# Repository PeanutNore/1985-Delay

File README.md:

# 1985-Delay
A Digital Delay pedal for guitar built around the AVR128DA28 MCU
    
This program is distributed in the hope that it will be useful,
but WITHOUT ANY WARRANTY; without even the implied warranty of
MERCHANTABILITY or FITNESS FOR A PARTICULAR PURPOSE.

 * Copyright 2025 Samuel Brown. All Rights Reservered.
 * 
 * Licensed under Creative Commons CC-BY-NC-SA 4.0
 * https://creativecommons.org/licenses/by-nc-sa/4.0/
 * 
 * You are free to share and adapt this software for non-
 * commercial purposes provided that you give appropriate 
 * credit and attribution, and distribute your contributions 
 * under the same CC-BY-NC-SA license.
 * 
 * For commercial licensing contact sam.brown.rit08@gmail.com

The maximum delay time available depends on the sample rate used and the bit depth of delay samples.
Main branch (1985_Delay) provides 1.4 seconds of delay at 10kHz and 8 bits and is tested and working with minor issues.
Highres branch (1985_Delay_Highres) provides 700ms of delay at 10kHz and 12 bits and is untested.

Adjust the sample rate as desired to balance available delay time and audio quality.

To use this software you will need:
* Arduino IDE version 1.8.19 or greater
* DxCore library for AVR128DA28 support (https://github.com/SpenceKonde/DxCore)
* Any USB to UPDI programmer. I recommend the Adafruit UPDI Friend because it is easy to use and under $20
* An AVR128DA28 MCU and appropriate supporting circuitry. Refer to the KiCad schematic and board files included in this repository.

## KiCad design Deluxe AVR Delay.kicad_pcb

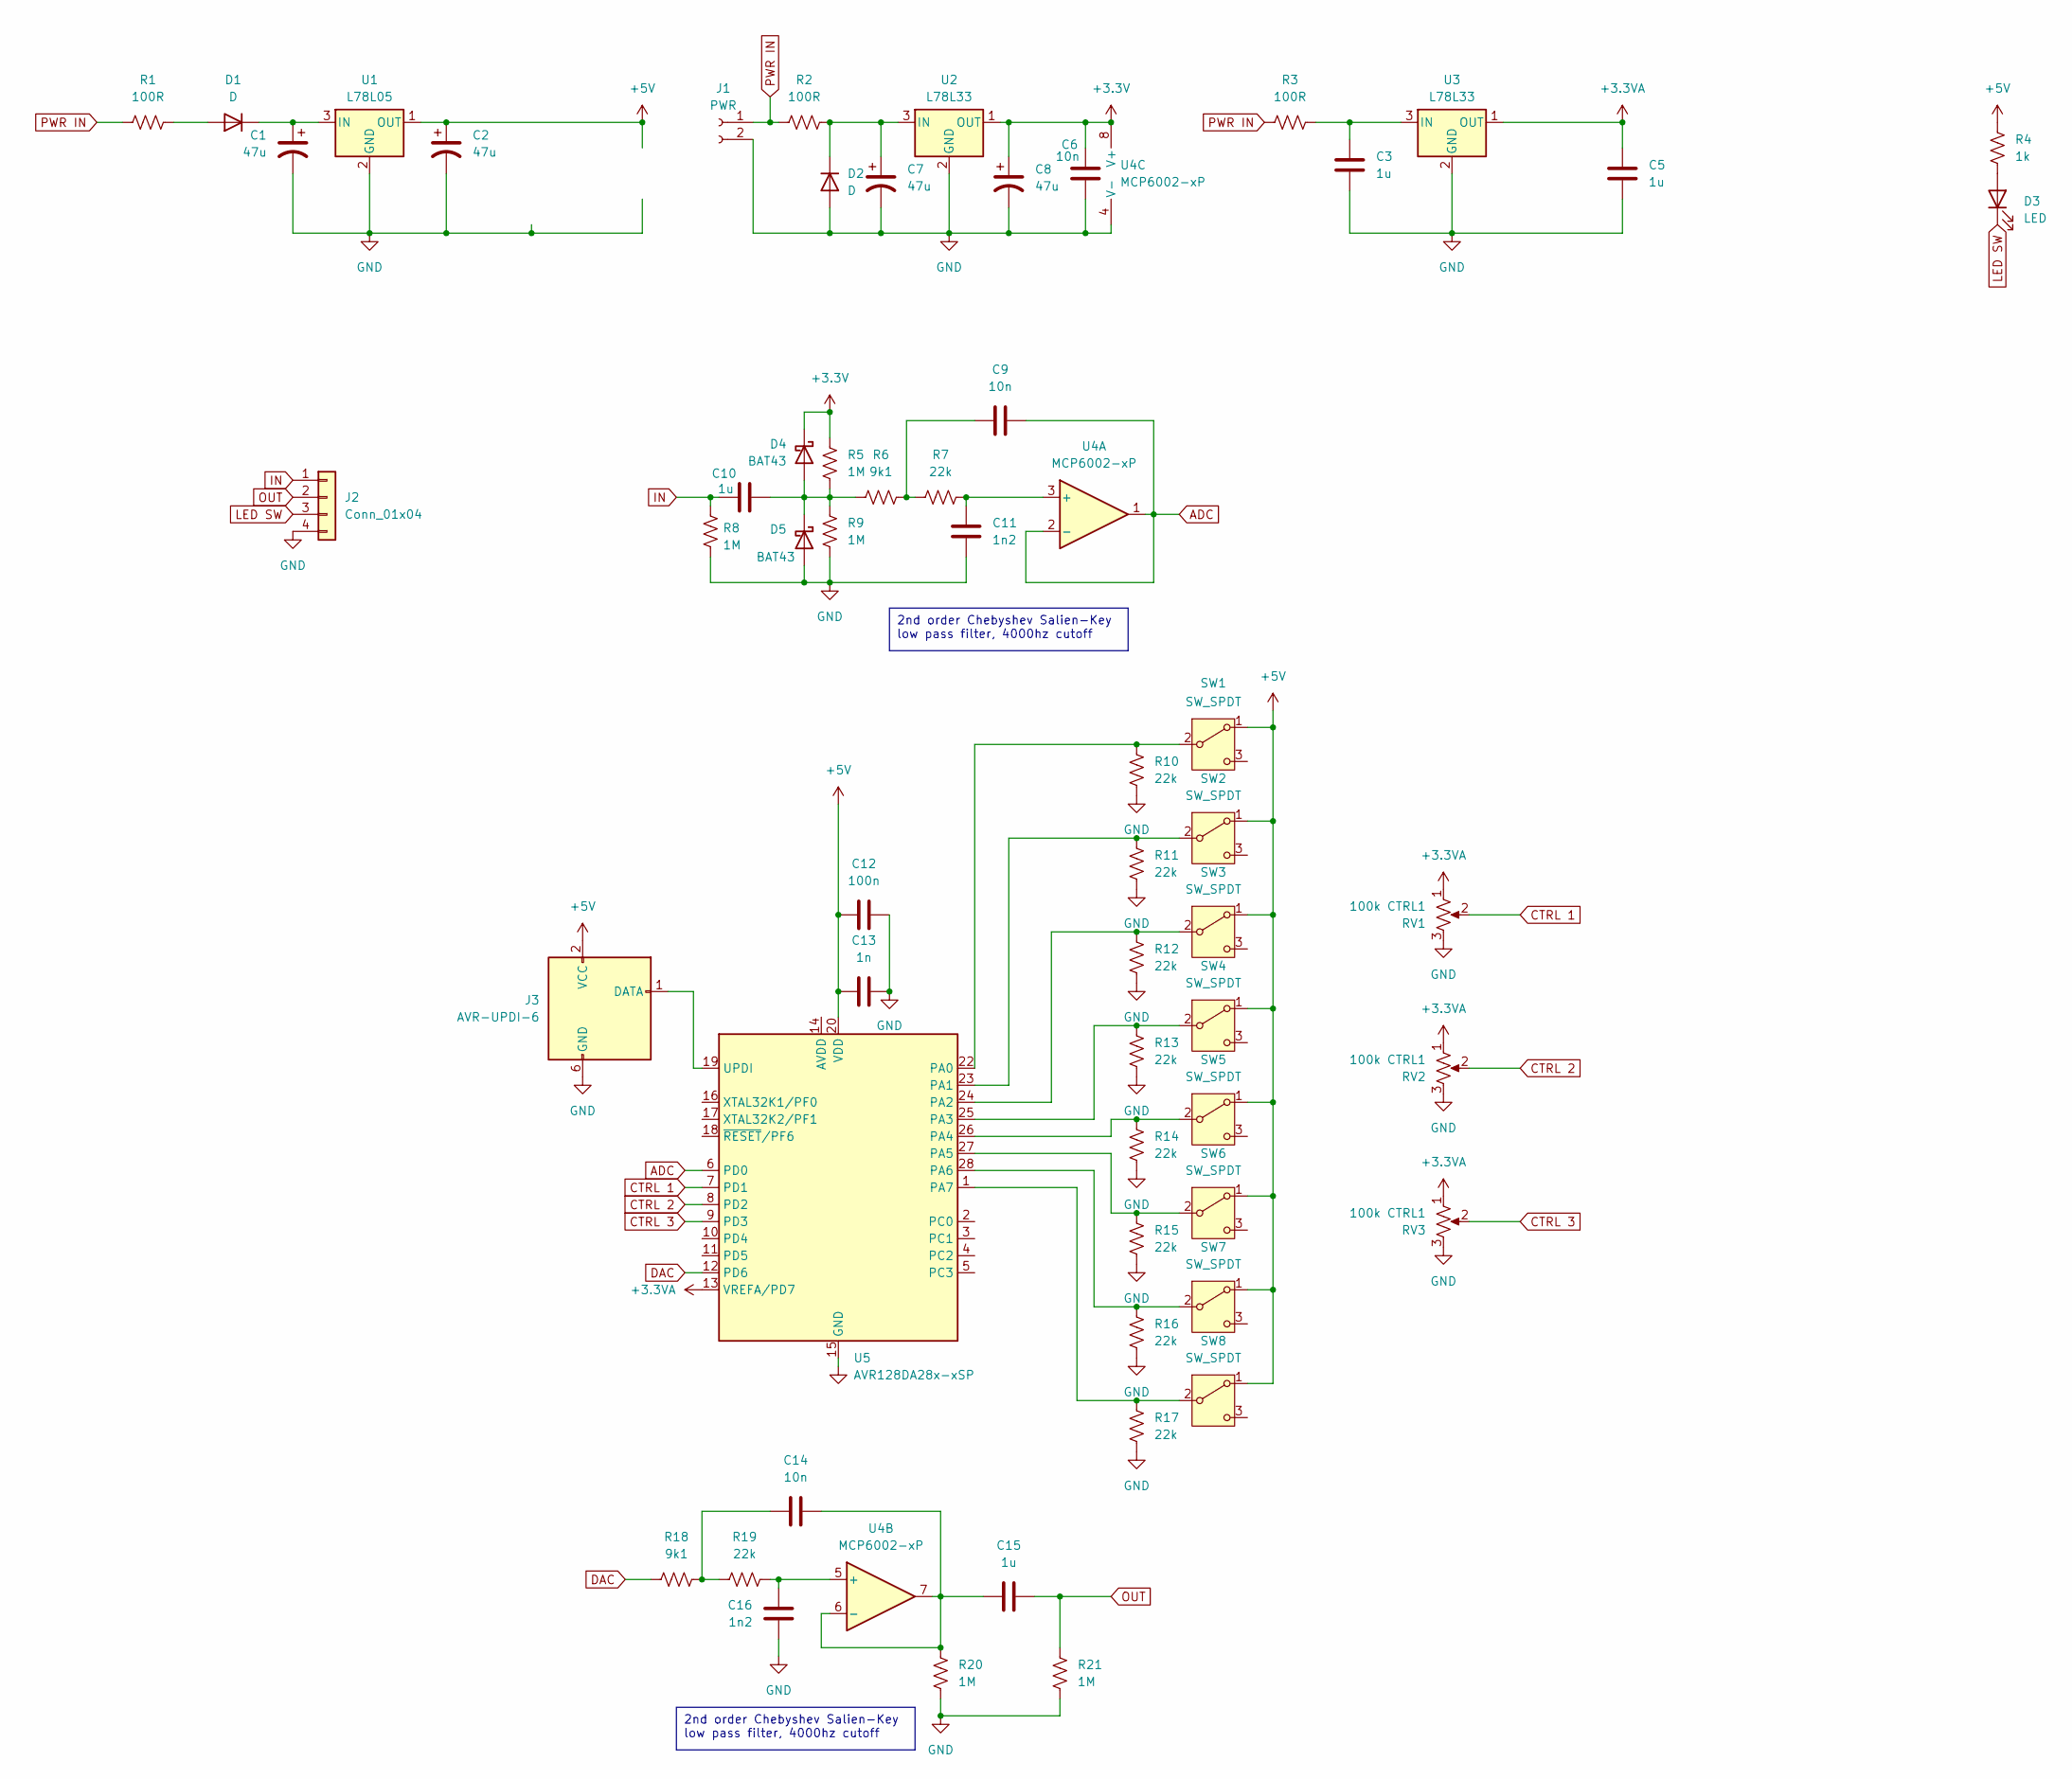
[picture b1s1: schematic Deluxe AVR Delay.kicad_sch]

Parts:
C1, C2, C7, C8: 47u; CP_Radial_D5.0mm_P2.50mm
C3, C5: 1u; C_1210_3225Metric
C6, C9, C14: 10n; C_0603_1608Metric
C10, C15: 1u; C_Rect_L7.0mm_W6.5mm_P5.00mm
C11, C16: 1n2; C_0603_1608Metric
C12: 100n; C_0603_1608Metric
C13: 1n; C_0603_1608Metric
D1, D2: D; D_DO-35_SOD27_P7.62mm_Horizontal
D3: LED; LED_D3.0mm
D4, D5: BAT43; D_DO-35_SOD27_P7.62mm_Horizontal
J1: PWR; PinHeader_1x02_P2.54mm_Vertical
J2: Conn_01x04; PinHeader_1x04_P2.54mm_Vertical
J3: AVR-UPDI-6; PinHeader_2x03_P2.54mm_Vertical
R1, R2, R3: 100R; R_Axial_DIN0207_L6.3mm_D2.5mm_P7.62mm_Horizontal
R4: 1k; R_0805_2012Metric
R5, R8, R9, R20, R21: 1M; R_0805_2012Metric
R6, R18: 9k1; R_0805_2012Metric
R7, R10, R11, R12, R13, R14, R15, R16, R17, R19: 22k; R_0805_2012Metric
RV1, RV2, RV3: 100k CTRL1; RV16AF-41
SW1, SW2, SW3, SW4, SW5, SW6, SW7, SW8: SW_SPDT; 2MS1T1B3M2QES
U1: L78L05; SOT-89-3
U2, U3: L78L33; SOT-89-3
U4: MCP6002-xP; DIP-8_W7.62mm_Socket
U5: AVR128DA28x-xSP; DIP-28_W7.62mm

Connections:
+3.3V: C6.1, C8.1, D4.1 (K), R5.1, U2.1 (OUT), U4.8 (V+)
+3.3VA: C5.2, RV1.1, RV2.1, RV3.1, U3.1 (OUT), U5.13 (VREFA/PD7)
+5V: C2.1, C12.1, C13.1, J3.2 (VCC), R4.1, SW1.1 (A), SW2.1 (A), SW3.1 (A), SW4.1 (A), SW5.1 (A), SW6.1 (A), SW7.1 (A), SW8.1 (A), U1.1 (OUT), U5.20 (VDD)
ADC: C9.2, U4.1, U4.2 (-), U5.6 (PD0)
CTRL 1: RV1.2, U5.7 (PD1)
CTRL 2: RV2.2, U5.8 (PD2)
CTRL 3: RV3.2, U5.9 (PD3)
DAC: R18.1, U5.12 (PD6)
GND: C1.2, C2.2, C3.1, C5.1, C6.2, C7.2, C8.2, C11.2, C12.2, C13.2, C16.2, D2.2 (A), D5.2 (A), J1.2, J2.4, J3.6 (GND), R8.2, R9.2, R10.1, R11.1, R12.1, R13.1, R14.1, R15.1, R16.1, R17.1, R20.2, R21.2, RV1.3, RV2.3, RV3.3, U1.2 (GND), U2.2 (GND), U3.2 (GND), U4.4 (V-), U5.15 (GND), U5.21 (GND)
IN: C10.1, J2.1, R8.1
LED SW: D3.1 (K), J2.3
unnamed: C9.1, R6.2, R7.1
unnamed: C14.1, R18.2, R19.1
unnamed: D1.2 (A), R1.2
unnamed: C1.1, D1.1 (K), U1.3 (IN)
unnamed: C7.1, D2.1 (K), R2.2, U2.3 (IN)
unnamed: D3.2 (A), R4.2
unnamed: C10.2, D4.2 (A), D5.1 (K), R5.2, R6.1, R9.1
unnamed: J3.1 (DATA), U5.19 (UPDI)
unnamed: R10.2, SW1.2 (B), U5.22 (PA0)
unnamed: R11.2, SW2.2 (B), U5.23 (PA1)
unnamed: R12.2, SW3.2 (B), U5.24 (PA2)
unnamed: R13.2, SW4.2 (B), U5.25 (PA3)
unnamed: R14.2, SW5.2 (B), U5.26 (PA4)
unnamed: R15.2, SW6.2 (B), U5.27 (PA5)
unnamed: R16.2, SW7.2 (B), U5.28 (PA6)
unnamed: R17.2, SW8.2 (B), U5.1 (PA7)
unnamed: C3.2, R3.2, U3.3 (IN)
unnamed: C11.1, R7.2, U4.3 (+)
unnamed: C16.1, R19.2, U4.5 (+)
unnamed: C14.2, C15.1, R20.1, U4.6 (-), U4.7
OUT: C15.2, J2.2, R21.1
PWR IN: J1.1, R1.1, R2.1, R3.1

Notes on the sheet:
2nd order Chebyshev Salien-Key low pass filter, 4000hz cutoff

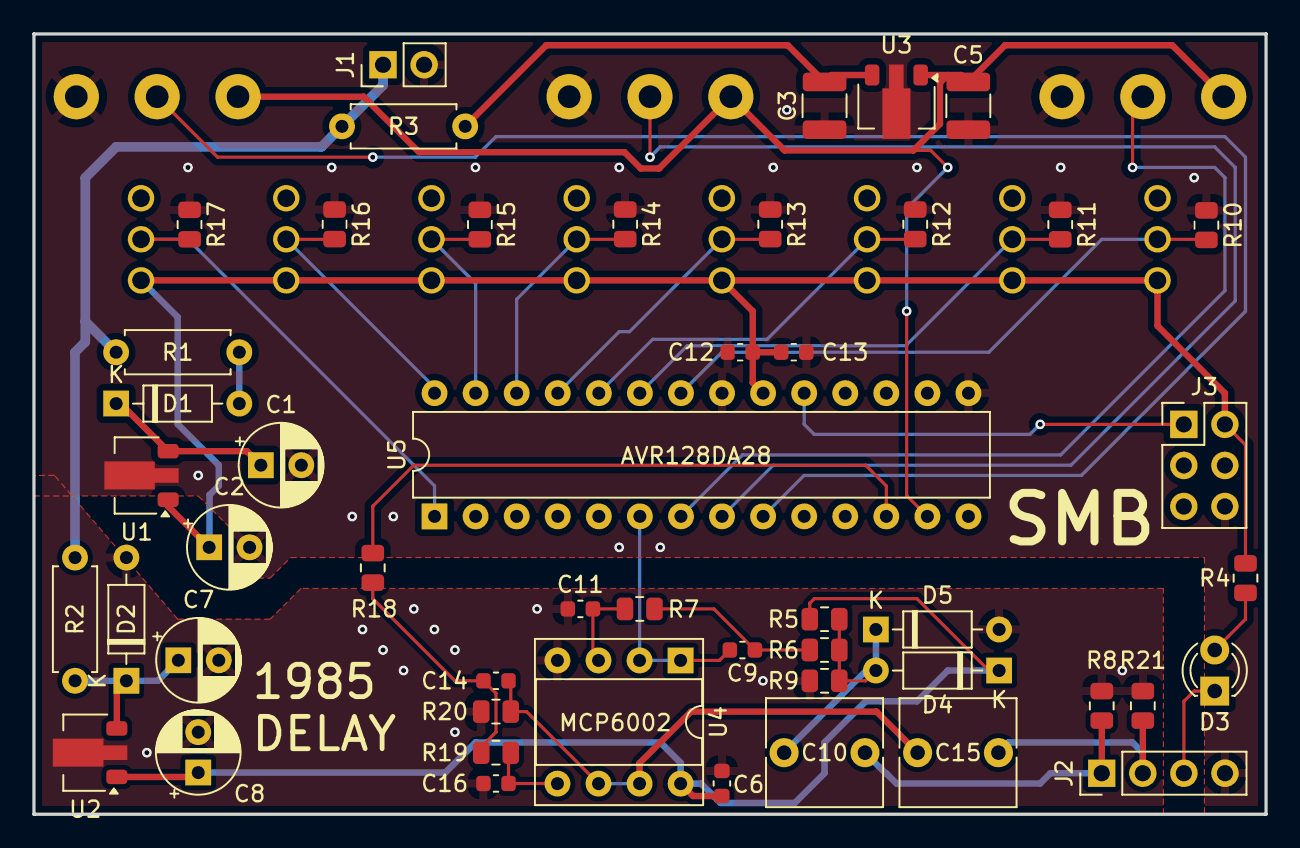
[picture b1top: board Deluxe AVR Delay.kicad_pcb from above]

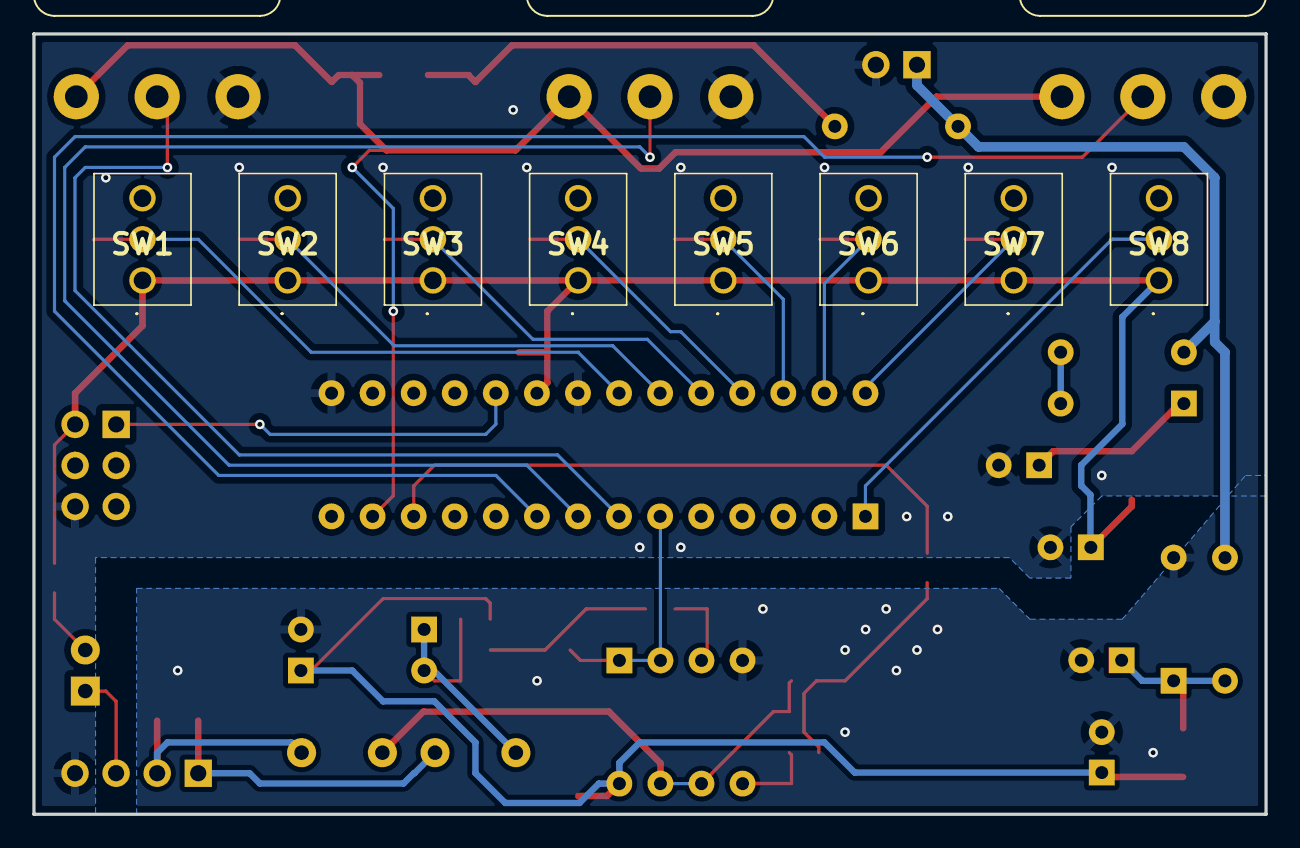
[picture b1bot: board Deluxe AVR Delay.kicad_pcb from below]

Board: 2 copper layers, 76.2 x 48.3 mm, 60 parts (11 on the bottom side), 33 nets.

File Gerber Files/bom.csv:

Designator,Footprint,Quantity,Value,LCSC Part #
"C11, C16",603,2,1n2,
C12,603,1,100n,
C13,603,1,1n,
"C14, C6, C9",603,3,10n,
"C3, C5",1210,2,1u,
"R10, R11, R12, R13, R14, R15, R16, R17, R19, R7",805,10,22k,
"R18, R6",805,2,9k1,
"R20, R21, R5, R8, R9",805,5,1M,
R4,805,1,1k,
U1,SOT-89-3,1,L78L05,
"U2, U3",SOT-89-3,2,L78L33,

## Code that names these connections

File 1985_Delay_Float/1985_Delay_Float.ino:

//Pin Assignments
uint8_t OutputPin = PIN_PD6;
uint8_t InputPin = PIN_PD0;
uint8_t TimePin = PIN_PD2;
uint8_t MixPin = PIN_PD1;
uint8_t FbkPin = PIN_PD3;
//Audio Samples
int16_t inSample;
int16_t delaySample;
float drySample;
float wetSample;
float storeSample;
float outSample;
int16_t intSample;
uint16_t dacSample;
int16_t delayArray[4096];

//Step Counters
uint16_t sampleStep = 0;
uint16_t delayStep = 0;

//Controls
uint16_t mixRaw = 0;
float mixFactor = 0.0;
uint16_t fbkRaw = 0;
float fbkFactor = 0.0;
uint16_t delaySet = 0;
uint16_t delayTimeNew = 0;
uint16_t delayTime = 0;

ISR(TCA0_OVF_vect) {
  //experiment here - clearing the interrupt flag first
  TCA0.SINGLE.INTFLAGS = TCA_SINGLE_OVF_bm;                 //clear the interrupt flags
  //get the input as a signed int
  inSample = analogRead(InputPin) - 2048;
  //get the signed int delayed sample
  delaySample = delayArray[delayStep];
  
  //convert the dry sample to a float between 1 and -1
  drySample = inSample / 2048.0;
  //convert the wet sample to a float between 1 and -1
  wetSample = delaySample / 2048.0;
  //prepare the sample to store in the array by starting with the feedback
  storeSample = wetSample;
  //attenuate the feedback
  storeSample *= fbkFactor;
  //add the dry sample
  storeSample += drySample;
  //convert to signed int
  delaySample = storeSample * 2048;
  //store the signed int sample in the delay
  delayArray[sampleStep] = delaySample;
  //attenuate the wet sample
  wetSample *= mixFactor;
  //combine the dry and wet samples together
  outSample = drySample + wetSample;
  //convert back to a signed int
  intSample = outSample * 2048;
  //constrain to the limits of the dac and make it unsigned
  if(intSample > 2047){intSample = 2047;}
  else if (intSample < -2048){intSample = -2048;}
  dacSample = intSample + 2048;
  dacSample = dacSample >> 2;
  //output to dac
  DAC0.DATAL = dacSample << 6;
  DAC0.DATAH = dacSample >> 2;
  //read the controls
  mixRaw = 4095 - (analogRead(MixPin) & 0b0000111111111100);
  mixFactor = mixRaw / 4095.0;
  fbkRaw = 4095 - (analogRead(FbkPin) & 0b0000111111111100);
  fbkFactor = fbkRaw / 4095.0;
  delayTimeNew = 4095 - (analogRead(TimePin) & 0b0000111111111100);
  if(delayTime < delayTimeNew){delayTime++;}
  else if (delayTime > delayTimeNew){delayTime--;}
  //increment the steps
  sampleStep++;
  sampleStep &= 0x0FFF;
  delayStep = sampleStep - delayTime;
  delayStep &= 0x0FFF;
  
}

void setup() {
  // put your setup code here, to run once:
for (int i = 0; i < 4096; i++){
  delayArray[i] = 0.0;
}
pinMode(OutputPin, OUTPUT);
pinMode(InputPin, INPUT);
pinMode(TimePin, INPUT);
pinMode(MixPin, INPUT);
pinMode(FbkPin, INPUT);
analogReference(EXTERNAL);
DACReference(EXTERNAL); //found to be missing when testing on final hardware- not an issue on the breadboard running everything at 5V
analogReadResolution(12);
analogSampleDuration(0);

mixRaw = analogRead(MixPin);
delayTime = 4095 - (analogRead(TimePin) & 0b0000111111111100);
mixFactor = mixRaw / 4095.0;

DAC0.DATAL = 0b00000000;
DAC0.DATAH = 0b10000000;
DAC0.CTRLA = 0b11000001;
takeOverTCA0();
TCA0.SINGLE.INTFLAGS = TCA_SINGLE_OVF_bm;
TCA0.SINGLE.INTCTRL  = 0b00000001; // overflow interrupt every PER cycles
TCA0.SINGLE.CTRLA    = TCA_SINGLE_CLKSEL_DIV1_gc; // Clock prescaler / 1 (24 MHz)    
TCA0.SINGLE.PER      = 1000;        // 300 * 8 = 2400 clocks, for a 10kHz sample rate, 200 * 8 = 1600 clocks 15kHz sample rate, 150 * 8 = 1200 clocks 20kHz sample rate, 125 * 8 = 1000 clocks 24kHz sample rate
TCA0.SINGLE.CTRLA   |= 1;          // Enables the timer                 
}

void loop() {
  // put your main code here, to run repeatedly:

}

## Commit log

2025-02-11 Update README.md
    Added license information
2025-02-12 Delete 1985_Delay.ino
    Moved file into proper folder structure
2025-02-12 Delete 1985_Delay_Simple.ino
    Moved file into proper folder structure
2025-02-13 Add files via upload
    Fixed missing step counter increment causing only dry signal to be heard
2025-02-13 Add files via upload
    reversed order of mix lookups to match the sweep of the potentiometer
2025-02-14 New High Resolution Mode
    This (as yet untested) mode changes the delay array to uint16_t and stores the full resolution sample in the delay array, at the cost of halving the amount of delay time available (approximately 700m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
2025-02-14 Added tips for customization
2025-02-15 Increased sample rate. Tested, working.
2025-02-18 Multiple enhancements & possible fix for Issue #2
    - Experimental changes to interrupt timer
    - Tested on final hardware & working
    - Added line to discard very small feedback samples to possibly fix issue #2
2025-02-18 Added Gerber files for ordering PCBs
    I have assembled and validated one of these boards that I had produced and assembled with SMD components by JLCPCB.
    WARNING!
    WHEN ORDERING ASSEMBLED BOARDS, CONFIRM THE VOLTAGE REGULATORS ARE ORIENTED CORRECTLY BEFORE PLACING AN ORDER!
    DAMAGE MAY RESULT IF THE VOLTAGE REGULATORS ARE INSTALLED BACKWARDS.
2025-02-18 Updated DACReference() to EXTERNAL
    This was missing from previous versions - on the breadboard it didn't matter since everything was at 5V anyway but on final hardware the analog side runs at 3.3v
2025-04-12 Experimenting with a simplified mixing method
    This is a standard delay that attempts to simplify the way that feedback and dry signal is mixed and hopefully improve audio quality. Also reduces the resolution of the delay control to 8 bit to mayb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
2026-03-27 Added new Floating Point version
    1985 Delay Float offers an improved noise floor and superior feedback and mix controls at the expense of sample rate.
    I think it sounds really cool.
2026-03-27 Change delaySample scaling factor from 4095 to 2048
    This fixes a typo
